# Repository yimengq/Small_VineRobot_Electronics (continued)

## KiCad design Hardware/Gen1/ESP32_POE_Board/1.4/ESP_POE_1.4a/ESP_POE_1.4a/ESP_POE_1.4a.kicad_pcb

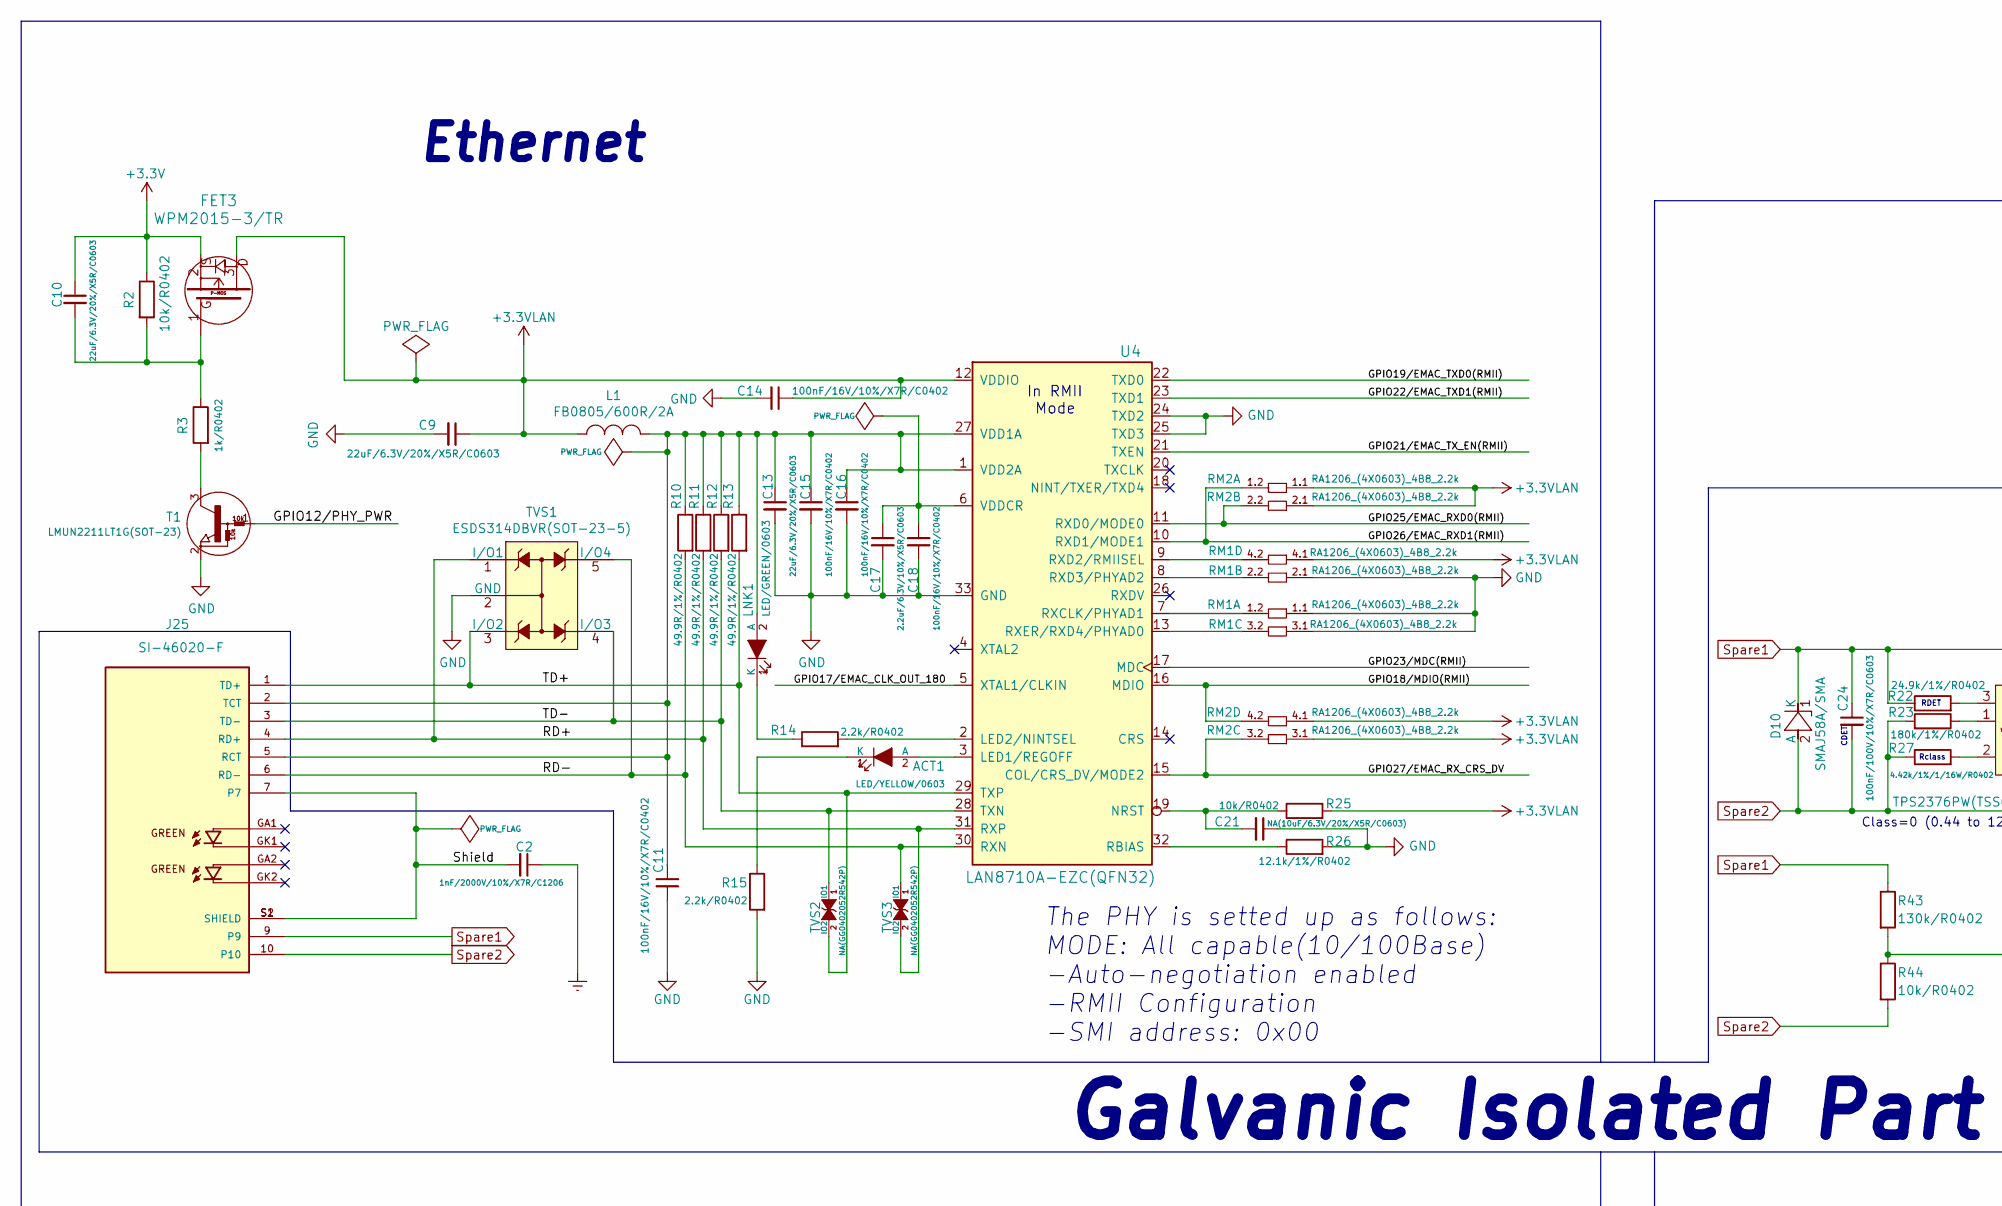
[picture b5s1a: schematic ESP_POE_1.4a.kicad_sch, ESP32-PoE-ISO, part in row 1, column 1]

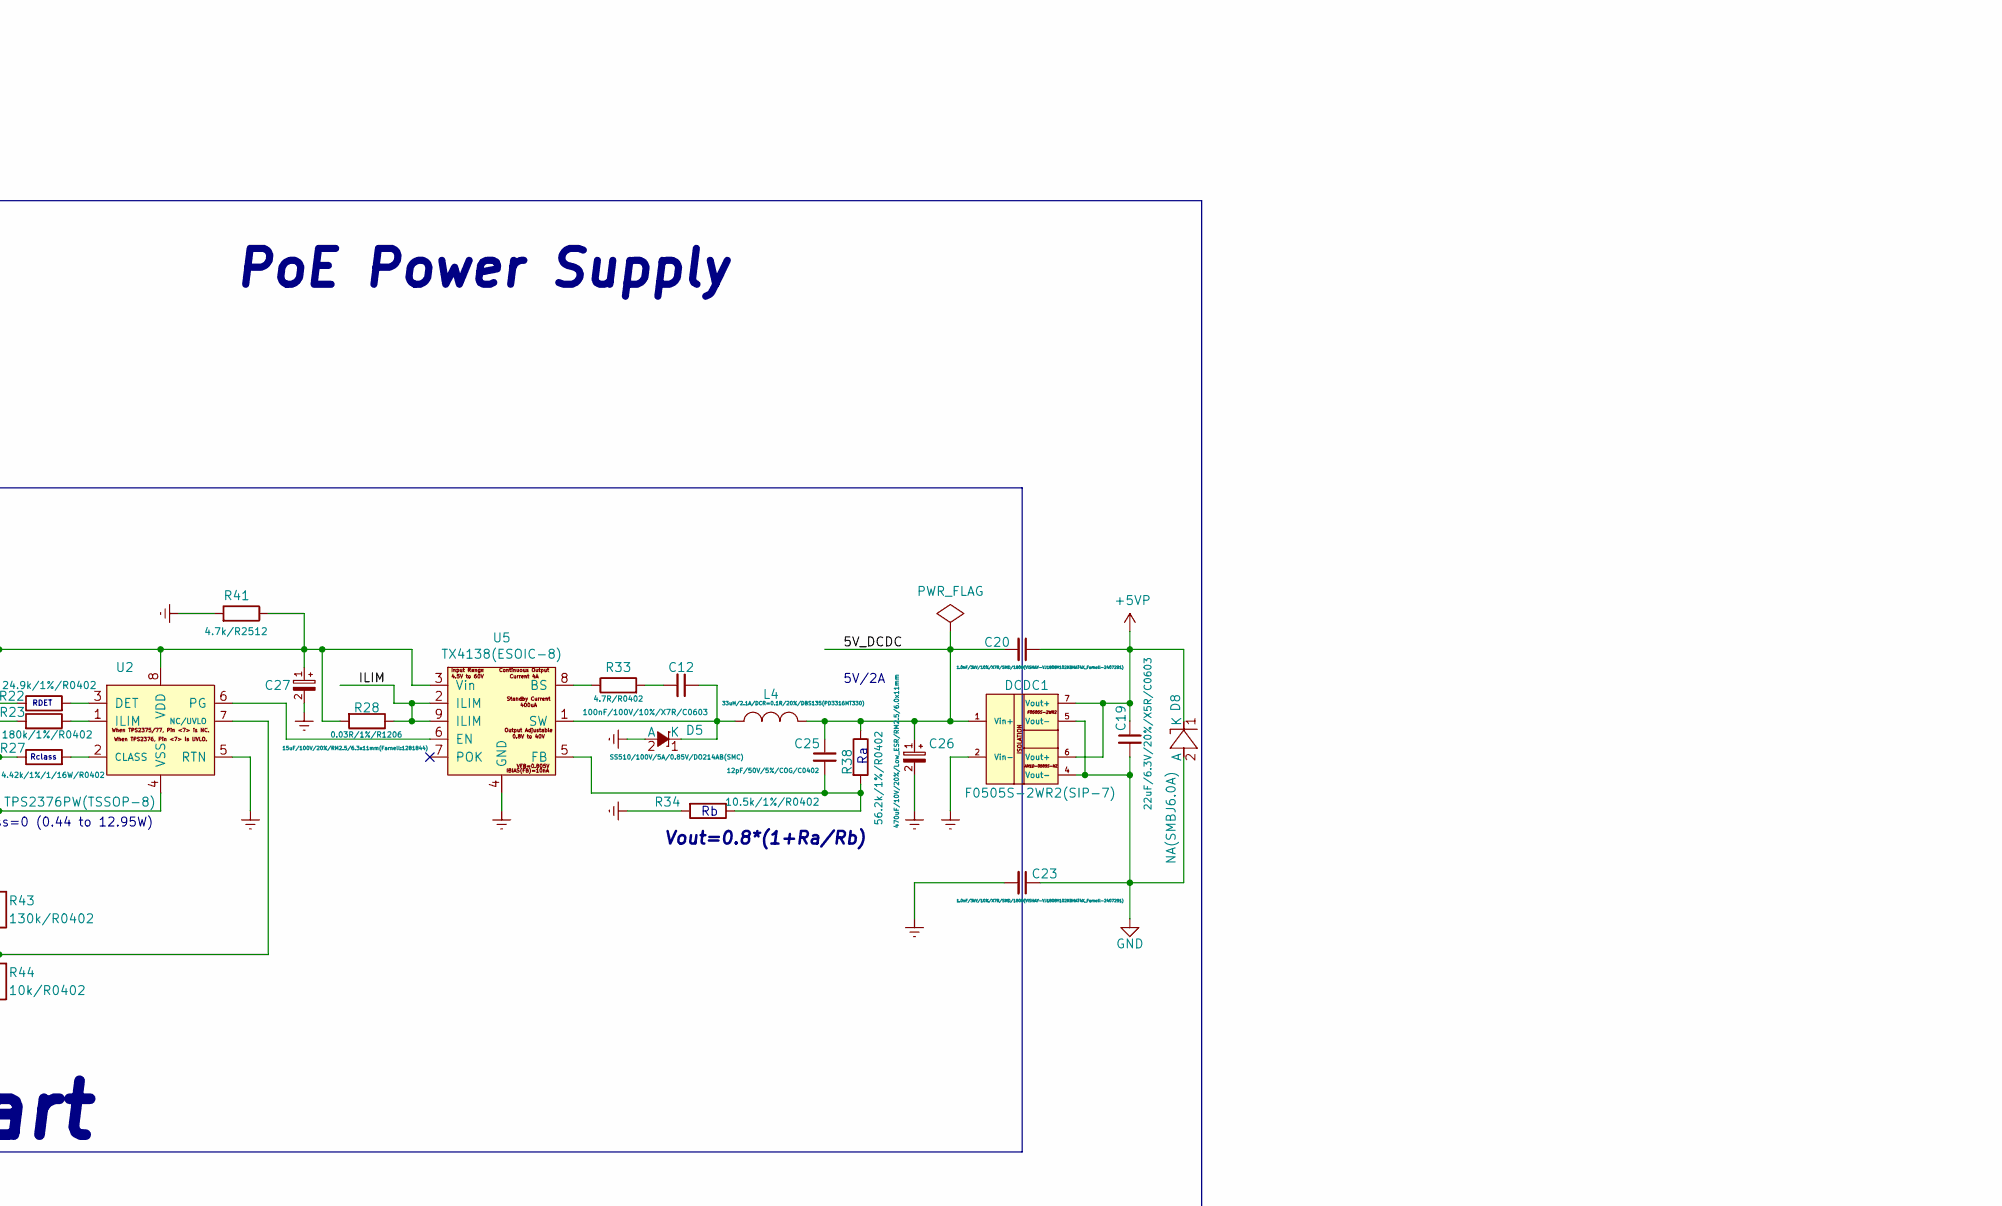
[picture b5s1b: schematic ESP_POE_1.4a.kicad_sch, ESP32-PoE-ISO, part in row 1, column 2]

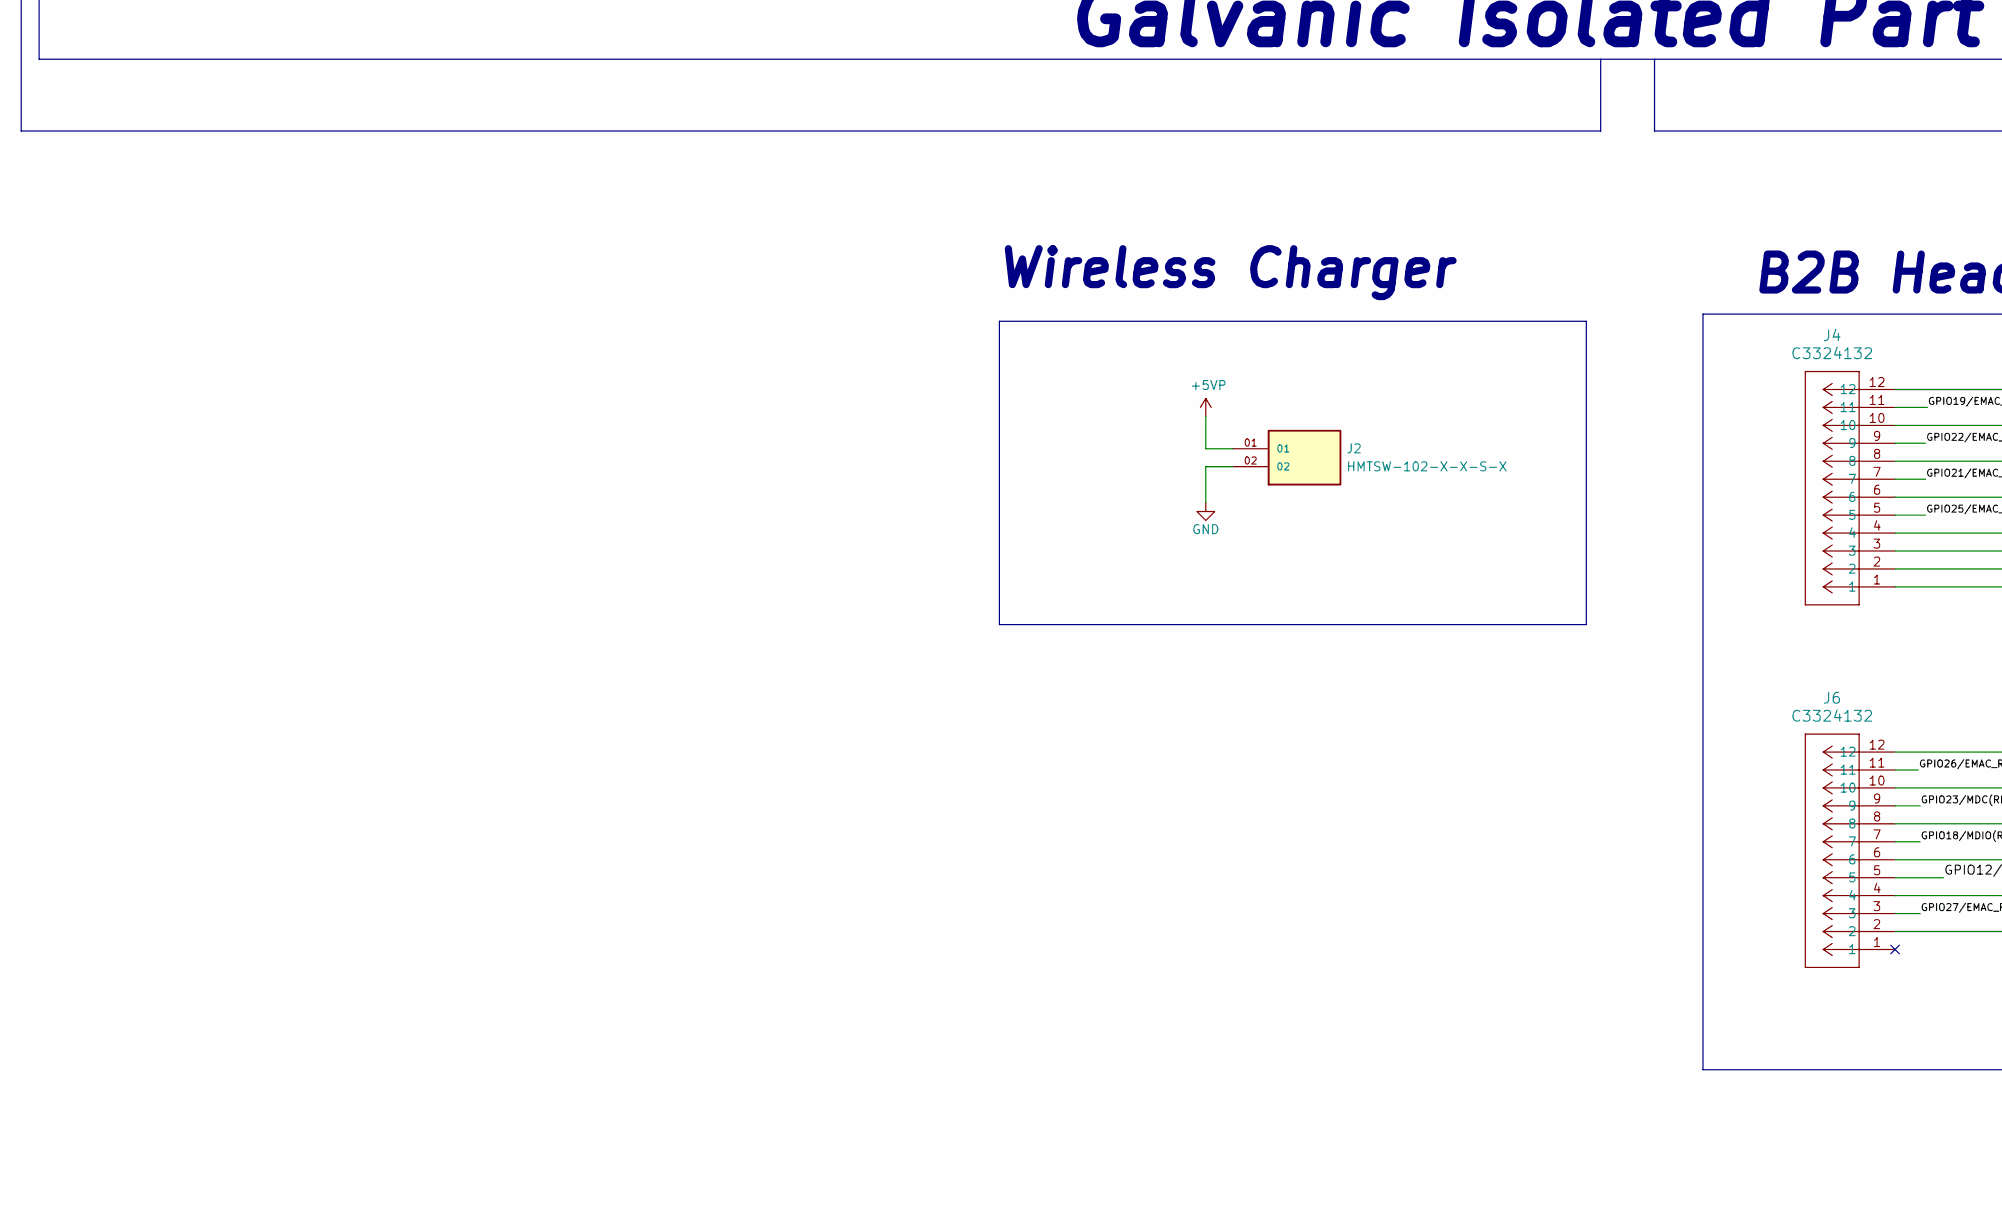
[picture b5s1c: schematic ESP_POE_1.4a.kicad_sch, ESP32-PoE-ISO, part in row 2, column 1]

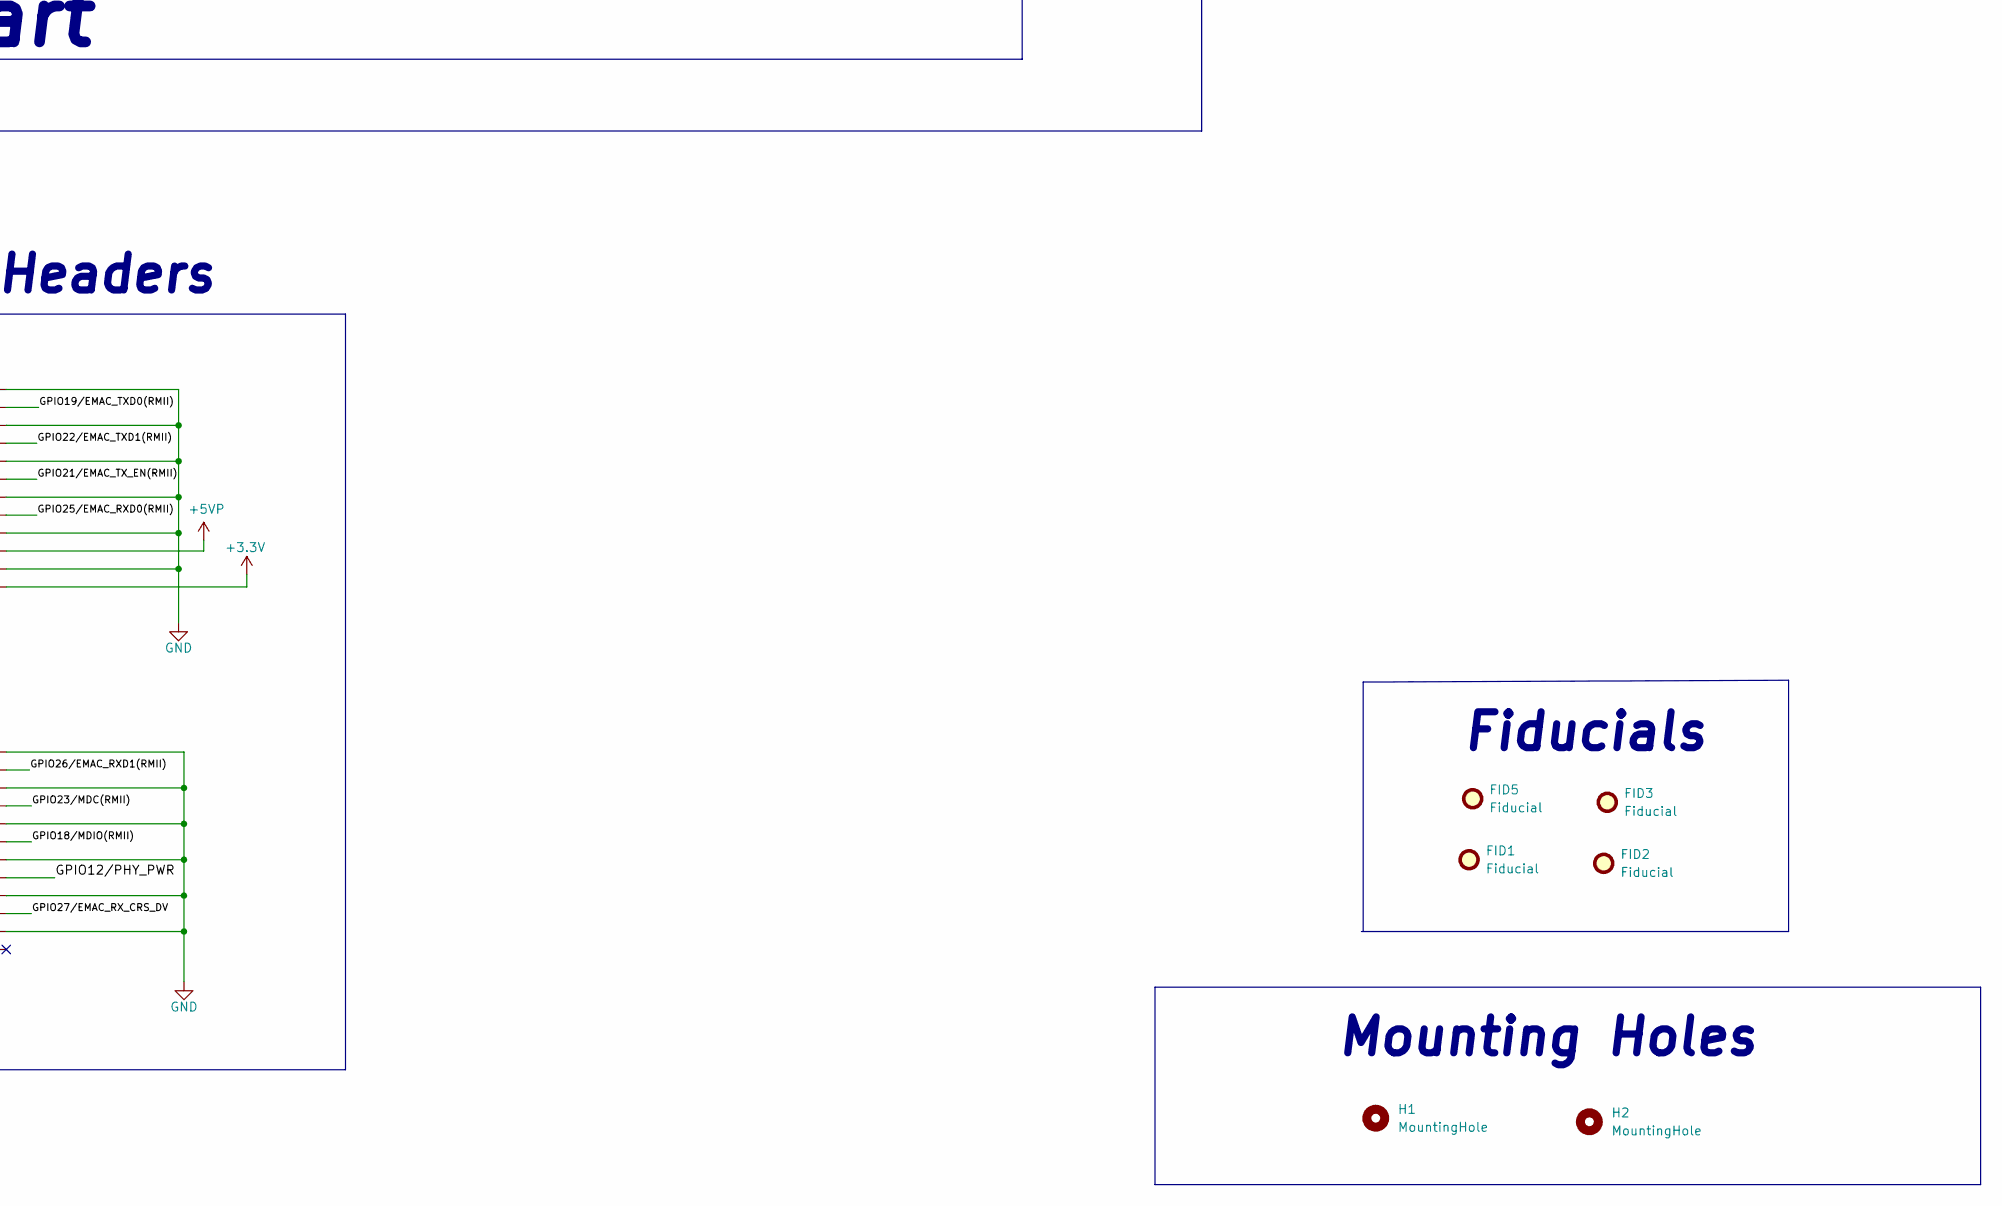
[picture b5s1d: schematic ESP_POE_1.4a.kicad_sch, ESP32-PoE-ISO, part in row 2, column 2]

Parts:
ACT1: LED/YELLOW/0603; LED_0603_KA; Mfr P/N 19-21/Y2C-CP1Q2B/4T
C2: 1nF/2000V/10%/X7R/C1206; C_1206_5MIL_DWS_ISO; Mfr P/N CC1206MKX7RDBB102
C9, C10, C13, C19: 22uF/6.3V/20%/X5R/C0603; C_0603_5MIL_DWS; Mfr P/N CL10A226MP8NUNE
C11, C14, C15, C16, C18: 100nF/16V/10%/X7R/C0402; C_0402_5MIL_DWS; Mfr P/N CC0402KRX7R7BB104
C12, C24: 100nF/100V/10%/X7R/C0603; C_0603_5MIL_DWS; Mfr P/N CC0603KRX7R9BB104
C17: 2.2uF/6.3V/10%/X5R/C0603; C_0603_5MIL_DWS; Mfr P/N CS1608X5R225K100NRB
C20, C23: 1.0nF/3kV/10%/X7R/SMD/1808(VISHAY-VJ1808Y102KBHAT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; C_1808(4520)_5MIL_DWS_ISO; Mfr P/N SCC1808X102K502TS
C21: NA(10uF/6.3V/20%/X5R/C0603); C_0603_5MIL_DWS; Mfr P/N CL10A106MA8NRNC
C25: 12pF/50V/5%/COG/C0402; C_0402_5MIL_DWS; Mfr P/N CL05C120JB51PNC
C26: 470uF/10V/20%/Low_ESR/RM2.5/6.0x11mm; CPOL-RM2.5mm_6.3x11mm_PTH; Mfr P/N GR477M016E12RR0EH4FP0
C27: 15uF/100V/20%/RM2.5/6.3x11mm(Farnell:1281844); CPOL-RM2.5mm_6.3x11mm_PTH; Mfr P/N EG22GM150F16OTMO
D5: SS510/100V/5A/0.85V/DO214AB(SMC); DO214AB(SMC)_1(K)-2(A); Mfr P/N SS510
D8: NA(SMBJ6.0A); DO214AA_1(K)-2(A)
D10: SMAJ58A/SMA; SMA-KA; Mfr P/N SMAJ58A-TR
DCDC1: F0505S-2WR2(SIP-7); SIP-7_Universal; Mfr P/N EVISUN F0505S-3WR2
FET3: WPM2015-3/TR; SOT23; Mfr P/N WPM2015-3/TR
FID1, FID2, FID3, FID5: Fiducial; Fiducial_0.5mm_Mask1.5mm
H1, H2: MountingHole; MountingHole_2.1mm
J2: HMTSW-102-X-X-S-X; SAMTEC_HMTSW-102-X-X-S-X; PARTREV A
J4, J6: C3324132; CONN_20021111-XX012XXLF_AMP; Mfr P/N 20021111-00012T4LF
J25: SI-46020-F; BEL_SI-46020-F; PARTREV C
L1: FB0805/600R/2A; L_0805_5MIL_DWS; Mfr P/N BLM21SP601SZ1D
L4: 33uH/2.1A/DCR=0.1R/20%/DBS135(PD3316MT330); IND_BOURNS_SRR1240; Mfr P/N SRR1240-330M
LNK1: LED/GREEN/0603; LED_0603_KA; Mfr P/N LTST-C190KGKT
R2, R25, R44: 10k/R0402; R_0402_5MIL_DWS; Mfr P/N RC0402FR-0710KL
R3: 1k/R0402; R_0402_5MIL_DWS; Mfr P/N RC0402FR-071KL
R10, R11, R12, R13: 49.9R/1%/R0402; R_0402_5MIL_DWS; Mfr P/N RC0402FR-0749R9P
R14, R15: 2.2k/R0402; R_0402_5MIL_DWS; Mfr P/N AC0402JR-072K2L
R22: 24.9k/1%/R0402; R_0402_5MIL_DWS; Mfr P/N RT0402BRD0724K9L
R23: 180k/1%/R0402; R_0402_5MIL_DWS; Mfr P/N AC0402FR-07180KL
R26: 12.1k/1%/R0402; R_0402_5MIL_DWS; Mfr P/N RT0402BRD0712K1L
R27: 4.42k/1%/1/16W/R0402; R_0402_5MIL_DWS; Mfr P/N RT0402BRD074K42L
R28: 0.03R/1%/R1206; R_1206_5MIL_DWS; Mfr P/N RL1206FR-070R03L
R33: 4.7R/R0402; R_0402_5MIL_DWS; Mfr P/N RC0402FR-074R7L
R34: 10.5k/1%/R0402; R_0402_5MIL_DWS; Mfr P/N RC0402FR-0710K5L
R38: 56.2k/1%/R0402; R_0402_5MIL_DWS; Mfr P/N AC0402FR-0756K2L
R41: 4.7k/R2512; R_2512_MM_DWS; Mfr P/N RC2512FK-074K7L
R43: 130k/R0402; R_0402_5MIL_DWS; Mfr P/N RT0402BRD07130KL
RM1, RM2: RA1206_(4X0603)_4B8_2.2k; R_MATRIX_4; Mfr P/N 4D03WGJ0222T5E
T1: LMUN2211LT1G(SOT-23); SOT23; Mfr P/N S-LMUN2211LT1G
TVS1: ESDS314DBVR(SOT-23-5); SOT-23-5; Mfr P/N ESDS314DBVR
TVS2, TVS3: NA(GG0402052R542P); D_0402_5MIL_DWS
U2: TPS2376PW(TSSOP-8); TSSOP-8_Pitch-0.65mm_Dimensions-4.40x3.00x1.20mm; Mfr P/N TPS2376PWR
U4: LAN8710A-EZC(QFN32); QFN32_EP(33)_5.00x5.00x0.90mm_Pitch_0.50mm; Mfr P/N LAN8710A-EZC-TR
U5: TX4138(ESOIC-8); ESOIC-8; Mfr P/N TX4138

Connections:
+3.3VLAN: C9.1, C14.1, FET3.3, L1.1, R25.2, RM1.4.1, RM2.1.1, RM2.2.1, RM2.3.1, RM2.4.1, U4.12 (VDDIO)
+3V3: C10.1, FET3.2, J4.1, R2.1
+5VP: C19.1, C20.1, D8.1 (K), DCDC1.6 (Vout+), DCDC1.7 (Vout+), J2.01, J4.3; also elsewhere on the board
/5V_DCDC: C20.2, C25.1, C26.1 (+), DCDC1.1 (Vin+), L4.2, R38.1
/GPIO12/PHY_PWR: J6.5, T1.1 (B)
/GPIO17/EMAC_CLK_OUT_180: U4.5 (XTAL1/CLKIN)
/GPIO18/MDIO(RMII): J6.7, RM2.4.2, U4.16 (MDIO)
/GPIO19/EMAC_TXD0(RMII): J4.11, U4.22 (TXD0)
/GPIO21/EMAC_TX_EN(RMII): J4.7, U4.21 (TXEN)
/GPIO22/EMAC_TXD1(RMII): J4.9, U4.23 (TXD1)
/GPIO23/MDC(RMII): J6.9, U4.17 (MDC)
/GPIO25/EMAC_RXD0(RMII): J4.5, RM2.2.2, U4.11 (RXD0/MODE0)
/GPIO26/EMAC_RXD1(RMII): J6.11, RM2.1.2, U4.10 (RXD1/MODE1)
/GPIO27/EMAC_RX_CRS_DV: J6.3, RM2.3.2, U4.15 (COL/CRS_DV/MODE2)
/ILIM: R28.1, U5.2 (ILIM), U5.9 (ILIM)
/RD+: J2.4 (RD+), R11.2, TVS1.1 (I/O1), TVS3.2 (IO2), U4.31 (RXP)
/RD-: J2.6 (RD-), R10.2, TVS1.5 (I/O4), TVS3.1 (IO1), U4.30 (RXN)
/Shield: C2.2, J2.7, J2.S1 (SHIELD), J2.S2 (SHIELD)
/TD+: J2.1 (TD+), R13.2, TVS1.3 (I/O2), TVS2.2 (IO2), U4.29 (TXP)
/TD-: J2.3 (TD-), R12.2, TVS1.4 (I/O3), TVS2.1 (IO1), U4.28 (TXN)
Earth: C2.1, C23.2, C26.2 (-), C27.2 (-), D5.2 (A), DCDC1.2 (Vin-), R34.2, R41.2, U2.5 (RTN), U5.4 (GND)
GND: C9.2, C11.2, C13.2, C14.2, C15.2, C16.2, C17.2, C18.2, C19.2, C21.1, C23.1, D8.2 (A), DCDC1.4 (Vout-), DCDC1.5 (Vout-), J2.02, J4.2, J4.4, J4.6, J4.8, J4.10, J4.12, J6.2, J6.4, J6.6, J6.8, J6.10, J6.12, R15.2, R26.2, RM1.1.1, RM1.2.1, RM1.3.1, T1.2 (E), TVS1.2 (GND), U4.24 (TXD2), U4.25 (TXD3), U4.33 (GND); also elsewhere on the board
unnamed: ACT1.2 (A), U4.3 (LED1/REGOFF)
unnamed: ACT1.1 (K), R15.1
unnamed: C10.2, FET3.1, R2.2, R3.1
unnamed: C12.2, R33.2
unnamed: C12.1, D5.1 (K), L4.1, U5.1 (SW)
unnamed: C11.1, C13.1, C15.1, C16.1, J2.2 (TCT), J2.5 (RCT), L1.2, LNK1.2 (A), R10.1, R11.1, R12.1, R13.1, U4.1 (VDD2A), U4.27 (VDD1A)
unnamed: LNK1.1 (K), R14.1
unnamed: R3.2, T1.3 (C)
unnamed: R27.2, U2.2 (CLASS)
unnamed: R22.2, U2.3 (DET)
unnamed: R23.1, U2.1 (ILIM)
unnamed: R43.2, R44.1, U2.7 (NC/UVLO)
unnamed: U2.6 (PG), U5.6 (EN)
unnamed: R14.2, U4.2 (LED2/NINTSEL)
unnamed: C21.2, R25.1, U4.19 (NRST)
unnamed: R26.1, U4.32 (RBIAS)
unnamed: RM1.1.2, U4.7 (RXCLK/PHYAD1)
unnamed: RM1.4.2, U4.9 (RXD2/RMIISEL)
unnamed: RM1.2.2, U4.8 (RXD3/PHYAD2)
unnamed: RM1.3.2, U4.13 (RXER/RXD4/PHYAD0)
unnamed: C17.1, C18.1, U4.6 (VDDCR)
unnamed: R33.1, U5.8 (BS)
unnamed: C25.2, R34.1, R38.2, U5.5 (FB)
Spare1: C24.1, C27.1 (+), D10.1 (K), J2.9, R22.1, R28.2, R41.1, R43.1, U2.8 (VDD), U5.3 (Vin)
Spare2: C24.2, D10.2 (A), J2.10, R23.2, R27.1, R44.2, U2.4 (VSS)

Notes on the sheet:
5V/2A
In RMII Mode
PoE Power Supply
Ethernet
B2B Headers
Class=0 (0.44 to 12.95W)
CDET
The PHY is setted up as follows: MODE: All capable(10/100Base) -Auto-negotiation enabled -RMII Configuration -SMI address: 0x00
Galvanic Isolated Part
Rclass
Vout=0.8*(1+Ra/Rb)
Mounting Holes
Fiducials
RDET
Wireless Charger

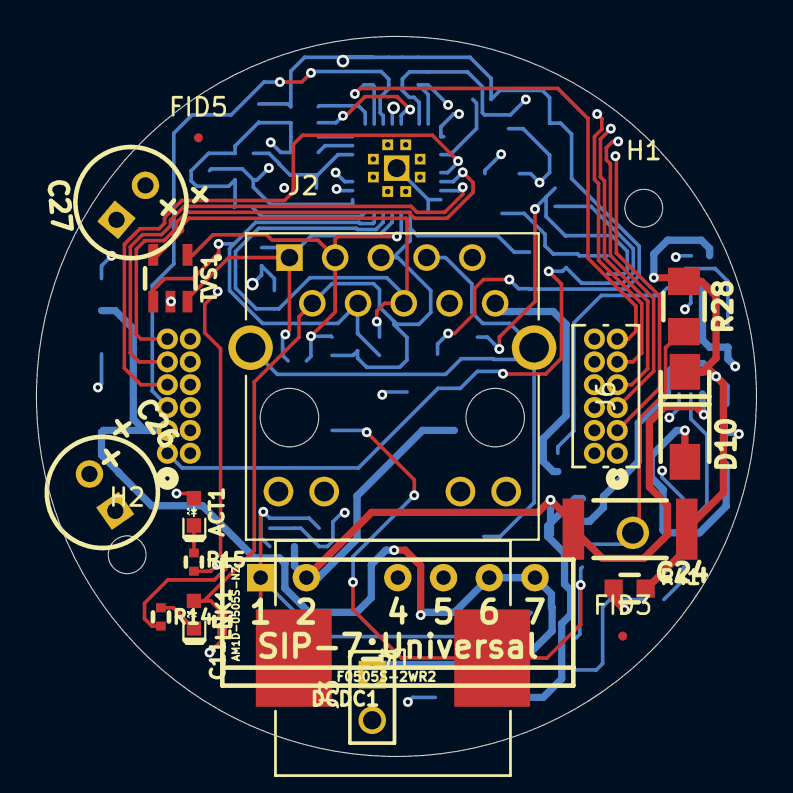
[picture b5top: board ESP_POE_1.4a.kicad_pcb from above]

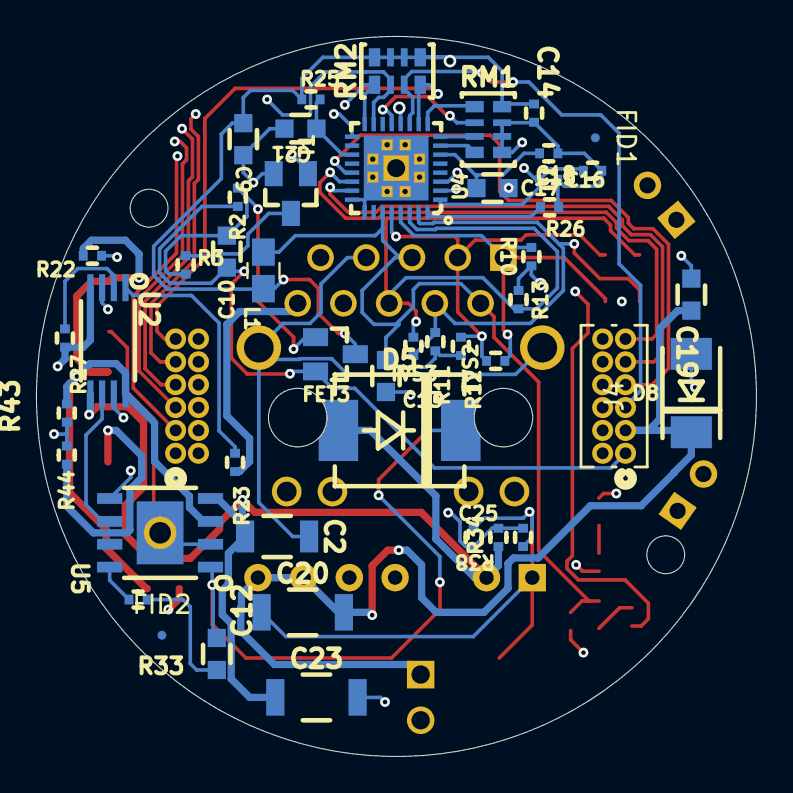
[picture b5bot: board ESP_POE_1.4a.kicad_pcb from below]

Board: 4 copper layers, 40.0 x 40.0 mm, 67 parts (46 on the bottom side), 46 nets.

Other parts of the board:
J3: HMTSW-102-X-X-S-X; SAMTEC_HMTSW-102-X-X-S-X

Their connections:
+5VP: J3.01; also elsewhere on the board
GND: J3.02; also elsewhere on the board

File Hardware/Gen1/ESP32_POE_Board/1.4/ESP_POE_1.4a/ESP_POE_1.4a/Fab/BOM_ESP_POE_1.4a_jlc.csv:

Comment,Designator,Footprint,JLCPCB Part #_optional_
LED/YELLOW/0603,ACT1,OLIMEX_LEDs-FP:LED_0603_KA,C2986008
1nF/2000V/10%/X7R/C1206,C2,OLIMEX_RLC-FP:C_1206_5MIL_DWS_ISO,C527363
22uF/6.3V/20%/X5R/C0603,"C9, C10, C13, C19",OLIMEX_RLC-FP:C_0603_5MIL_DWS,C86295
100nF/16V/10%/X7R/C0402,"C11, C14,C15,C16, C18",OLIMEX_RLC-FP:C_0402_5MIL_DWS,C60474
100nF/100V/10%/X7R/C0603,"C12, C24",OLIMEX_RLC-FP:C_0603_5MIL_DWS,C14663
2.2uF/6.3V/10%/X5R/C0603,C17,OLIMEX_RLC-FP:C_0603_5MIL_DWS,C5189830
1.0nF/3kV/10%/X7R/SMD/1808(VISHAY-VJ1808Y102KBHAT4X_Farnell-2407291),"C20, C23",OLIMEX_RLC-FP:C_1808(4520)_5MIL_DWS_ISO,C2939745
NA(10uF/6.3V/20%/X5R/C0603),C21,OLIMEX_RLC-FP:C_0603_5MIL_DWS,C96446
12pF/50V/5%/COG/C0402,C25,OLIMEX_RLC-FP:C_0402_5MIL_DWS,C472446
470uF/10V/20%/Low_ESR/RM2.5/6.0x11mm,C26,OLIMEX_RLC-FP:CPOL-RM2.5mm_6.3x11mm_PTH,C3039776
15uF/100V/20%/RM2.5/6.3x11mm(Farnell:1281844),C27,OLIMEX_RLC-FP:CPOL-RM2.5mm_6.3x11mm_PTH,C2841644
SS510/100V/5A/0.85V/DO214AB(SMC),D5,OLIMEX_Diodes-FP:DO214AB(SMC)_1(K)-2(A),C5339843
SMAJ58A/SMA,D10,OLIMEX_Diodes-FP:SMA-KA,C132936
,,,
WPM2015-3/TR,FET3,OLIMEX_Transistors-FP:SOT23,C6562215
HMTSW-102-X-X-S-X,J3,HMTSW-102-X-X-S-X:SAMTEC_HMTSW-102-X-X-S-X,C234182
C3324132,"J4, J6",CONN_20021111-XX012XXLF_AMP,C3324132
FB0805/600R/2A,L1,OLIMEX_RLC-FP:L_0805_5MIL_DWS,C2661781
LED/GREEN/0603,LNK1,OLIMEX_LEDs-FP:LED_0603_KA,C172883
10k/R0402,"R2, R25, R44",OLIMEX_RLC-FP:R_0402_5MIL_DWS,C60490
1k/R0402,R3,OLIMEX_RLC-FP:R_0402_5MIL_DWS,C106235
49.9R/1%/R0402,"R10,R11,R12,R13",OLIMEX_RLC-FP:R_0402_5MIL_DWS,C851839
2.2k/R0402,"R14, R15",OLIMEX_RLC-FP:R_0402_5MIL_DWS,C144718
24.9k/1%/R0402,R22,OLIMEX_RLC-FP:R_0402_5MIL_DWS,C852664
180k/1%/R0402,R23,OLIMEX_RLC-FP:R_0402_5MIL_DWS,C144794
12.1k/1%/R0402,R26,OLIMEX_RLC-FP:R_0402_5MIL_DWS,C281773
4.42k/1%/1/16W/R0402,R27,OLIMEX_RLC-FP:R_0402_5MIL_DWS,C513571
0.03R/1%/R1206,R28,OLIMEX_RLC-FP:R_1206_5MIL_DWS,C375524
4.7R/R0402,R33,OLIMEX_RLC-FP:R_0402_5MIL_DWS,C137962
10.5k/1%/R0402,R34,OLIMEX_RLC-FP:R_0402_5MIL_DWS,C171695
56.2k/1%/R0402,R38,OLIMEX_RLC-FP:R_0402_5MIL_DWS,C227142
4.7k/R2512,R41,OLIMEX_RLC-FP:R_2512_MM_DWS,C163339
130k/R0402,R43,OLIMEX_RLC-FP:R_0402_5MIL_DWS,C852515
RA1206_(4X0603)_4B8_2.2k,"RM1, RM2",OLIMEX_RLC-FP:R_MATRIX_4,C12001
LMUN2211LT1G(SOT-23),T1,OLIMEX_Transistors-FP:SOT23,C12775
ESDS314DBVR(SOT-23-5),TVS1,OLIMEX_Diodes-FP:SOT-23-5,C1847859
TPS2376PW(TSSOP-8),U2,OLIMEX_IC-FP:TSSOP-8_Pitch-0.65mm_Dimensions-4.40x3.00x1.20mm,C544899
LAN8710A-EZC(QFN32),U4,OLIMEX_IC-FP:QFN32_EP(33)_5.00x5.00x0.90mm_Pitch_0.50mm,C46185
TX4138(ESOIC-8),U5,OLIMEX_Regulators-FP:ESOIC-8,C329267

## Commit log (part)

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2024-10-28 starting schematics
2024-10-29 fixed
2024-10-29 dev board
2024-10-30 stuff
2024-11-01 Increase buffers to improve performance
2024-11-09 Improve performance with external oscillator EVB board
2024-11-13 Added cam webserver code
2024-11-14 Added in flash firmware
2024-11-21 Changes to init wifi and added Blink test
2024-11-23 Update IMU_test for different I2C pins
2024-11-26 Added I2C_Check
2024-11-26 Added PSRAM check
2024-11-27 Merged IMU, LED, and Cam code
2024-11-27 Added SDA/SCL pin fix
2024-12-10 Motor Pseudocode draft 1
2024-12-19 Some debug fixes for sense dev board
2025-01-12 Add reconnect to WiFi on disconnect
2025-01-15 Switch order of wifi and camera init
2025-01-25 Added basic ethernet test and documentation
2025-01-30 schematic for v2.1 dev board done. Footprints update progress. Layout will roll when footprints finalize
2025-02-02 Inner board 2.1 footprint links fixed (for future work) and more included. Layout will roll when footprints finalize
2025-02-02 Inner board 2.1 footprint links refactored (for future work) and more included. Layout will roll when footprints finalize
2025-02-05 Inner board 2.1 footprint links refactored (for future work) and added all links. Routing progress
2025-02-05 Routing progress. Mergedf 3.3v and 3v3
2025-02-05 Routing progress. Team meeting lead us to notice discrepancy. Dev board now in the hands of Rohan and Yimeng!
2025-02-06 new 2.2
2025-02-06 footprints on buttons
    stuff
2025-02-12 fix lib
2025-02-16 wait for testing result
2025-02-18 temp
2025-02-18 gerber
2025-02-18 gerbers
2025-02-18 cache
2025-02-21 Added motor support
2025-02-24 unsaved
2025-02-28 Modified UI for motor control, add keyboard support
2025-03-09 Changed imu pins for v3.1b
2025-03-10 Fixed motor functionality for ov5640 cam
2025-03-14 Fix documentation and motor pin
2025-03-14 Added UI tools
2025-03-19 Example PoE schematic
2025-04-10 Back to branch
2025-04-15 PoE V1
2025-04-16 Pinout for Xiao
2025-04-30 stufff
2025-05-05 updated BOM and Fab
2025-05-05 temp file
2025-06-11 Initial GUI for inpipe robot, showing video, and rotation data
2025-06-16 Joystick data connected to GUI
2025-06-16 Arrow visualization for joystick movement
2025-06-18 Fullscreen feature almost fully implemented
2025-06-18 Fullscreen partially implemented
2025-06-19 Switched to a main window
2025-06-19 Debugging fullscreen feature
2025-06-20 Fixed issue with fullscreen feature
2025-06-20 Modified x-direction of arrows in joystick visualizer
2025-06-20 Rough implementation of menu and zoom-in features
2025-06-30 1-way http streaming to python
2025-07-01 Added varying resolutions
2025-07-02 basic two way http
2025-07-03 init IMU/TOF telemetry code
2025-07-03 functional IMU/ToF code, placeholder data
2025-07-21 Made some aesthetic changes to GUI
2025-07-21 Format changes
2025-07-22 cleanup
2025-07-22 initial esp32 video/imu/orientation stream for frontend
2025-07-22 cleanup esp32 vid/data stream to GUI
2025-07-22 Current GUI with telemetry/video incorporated
2025-07-24 test script for asm330lhb
2025-07-25 asm330 unit fix
2025-07-25 changes to menu functionality
2025-07-25 tip-sensing board v4.2 upload
2025-07-25 new small changes
2025-07-25 working murata sch16t data reads
2025-07-25 cleaned up outerboard4.2 folder
2025-07-25 cleaned up some stuff
2025-07-25 cleaning
2025-07-29 working murata sch16t accel/gyro reading
2025-07-29 file rename
2025-07-29 cleanup sch16t
2025-07-31 Update localization placeholder
2025-08-05 Script for dead reckoning on gyroscope
2025-08-05 added servo test to test sequence
2025-08-05 readme added
2025-08-05 readme formatting
2025-08-05 readme edit
2025-08-05 added servo control to 2way streaming
2025-08-06 updated servo control for 2 servos
2025-08-07 Testing joystick connection to servo
2025-08-07 Radxa RTSP and UDP code (streaming)
2025-08-09 updated fab file for board4.2
2025-08-12 readme rtsp
2025-08-12 Commit on 11 Aug '25
2025-08-13 servo
2025-08-14 Debugging issue with sending servo commands in UI
2025-08-14 Debugging GUI with servo commands
2025-08-14 Ignore all .lck files
2025-08-14 Tip Sensing Full System
2025-08-14 Added Servo Control through SSH
2025-08-14 Separated camera to a different thread
2025-08-14 Added led code in both server and standalone
2025-08-15 servo fix
2025-08-15 add arduino updated camerawebserver_http
2025-08-15 cameraweb_http
2025-08-15 update ino and py for servo control
2025-08-16 clean up
2025-08-16 updaded arduino code
2025-08-17 update individual server and host
2025-08-17 server code ready
2025-08-17 host code ready
2025-08-17 organized code
2025-08-18 Create temp
2025-08-18 created branch and uploaded documentation for comms hub board
2025-08-18 pushed a compressed file
2025-08-18 deleted temp
2025-08-22 full code for vine front end
2025-08-22 new branch + arduino IMU
2025-08-26 Got IMU to sporadically work, need to figure out polling/checksum issue
2025-08-27 demo
2025-08-29 Got IMU to work over SPI
2025-08-29 Added readme for pinouts and IMU setup
2025-09-05 Demo code
2025-09-05 Added fake SPI code
2025-09-05 Updated LED
2025-09-05 GPIODV1
2025-09-09 fake spi led
2025-09-09 Added Imu Files (not integrated)
2025-09-09 PWM working again
2025-09-10 added led test code
2025-09-10 IMU and Fake SPI working and semi-integrated
2025-09-22 Added servo limits to prevent overcurrenting
2025-09-23 IMU_initial
2025-09-23 IMU_1
2025-09-23 update run_rtsp
2025-09-23 Fixed buffer overflow and wrong labeling
2025-09-24 Fixed servo limits
2025-09-29 bno055
2025-09-29 add bno055_server
2025-10-01 gen5board
2025-10-08 Fixed LED code (wrong GPIO version)
2025-10-16 imu working on radxa, working on graphing/graphic simulations
2025-10-16 new branch for IMU
2025-10-16 cleaning up
2025-10-17 adding graph and 3d model script
2025-10-21 visualization for local host:
2025-10-22 final
2025-10-24 add .gitignore for Kicad backups
2025-10-29 Esp32 Board added
2025-10-31 Updated power and esp32 boards
2025-10-31 imu and temp data progress
2025-10-31 updating
2025-10-31 adding imu to this branch
2025-11-06 editing host code
2025-11-06 host code
2025-11-06 editing server code
2025-11-28 done
2025-12-10 adding comments to cam
2025-12-18 Bring local RTSP camera changes onto http_streaming
2025-12-18 fixed path
2025-12-19 One motor ti drv working
2025-12-19 2 Motors working with 1 dac
2025-12-20 Circuit Schematic Draft for Motor Driver and Power Breakout Board
2025-12-20 Added another driver
2025-12-21 Added voltage and current monitoring
2025-12-27 Protoboard:
2025-12-27 Updated base station code to work with tip motors
2025-12-27 Modified host_modified
2025-12-28 Added server for tip motors
2025-12-28 Modified it for shoulder buttons and terminal commands
2025-12-31 Trying to get streaming to work
2025-12-31 sync
2025-12-31 Fixing rtsp pipeline issue
2025-12-31 updated build.launch
2025-12-31 More build launch
2025-12-31 Cleaned folder structure
2025-12-31 Trying to fix rtsp_server
2025-12-31 Stable TCP streaming code
2026-01-01 moved working rtsp server
2026-01-01 Stream and new motors working
2026-01-03 Added ROS2 versions of base station code
2026-01-03 ROS2 Stable
2026-01-03 Cleaned up some files
2026-01-03 Added velocity control for tip motors
2026-01-03 Added variable shoulder motor control
2026-01-03 added udp server code
2026-01-03 UDP and motors stable
2026-01-03 UDP base code
2026-01-05 Restructured files for only Radxa code
2026-01-05 Reformatted file structure with only base station code
2026-01-15 established dedicated Radxa branch and added dual camera + LED control
2026-01-16 IMU, Dual Cameras, LED, and Motors all working simultaneously
2026-01-16 IMU, Motors, LED, and Dual Cameras working
2026-02-10 Added Cable Reeling V2
2026-02-10 Added Power board V2
2026-02-24 Working with amazon motor
2026-02-24 Reorganized and archived non-server files
2026-02-24 Deleted Archive
2026-02-24 Tried using Codex to fix shutdown not occuring on Ctrl C
2026-02-24 Shutdown Fix
2026-02-24 Two stage shutdown
2026-03-09 Updated length Matching
